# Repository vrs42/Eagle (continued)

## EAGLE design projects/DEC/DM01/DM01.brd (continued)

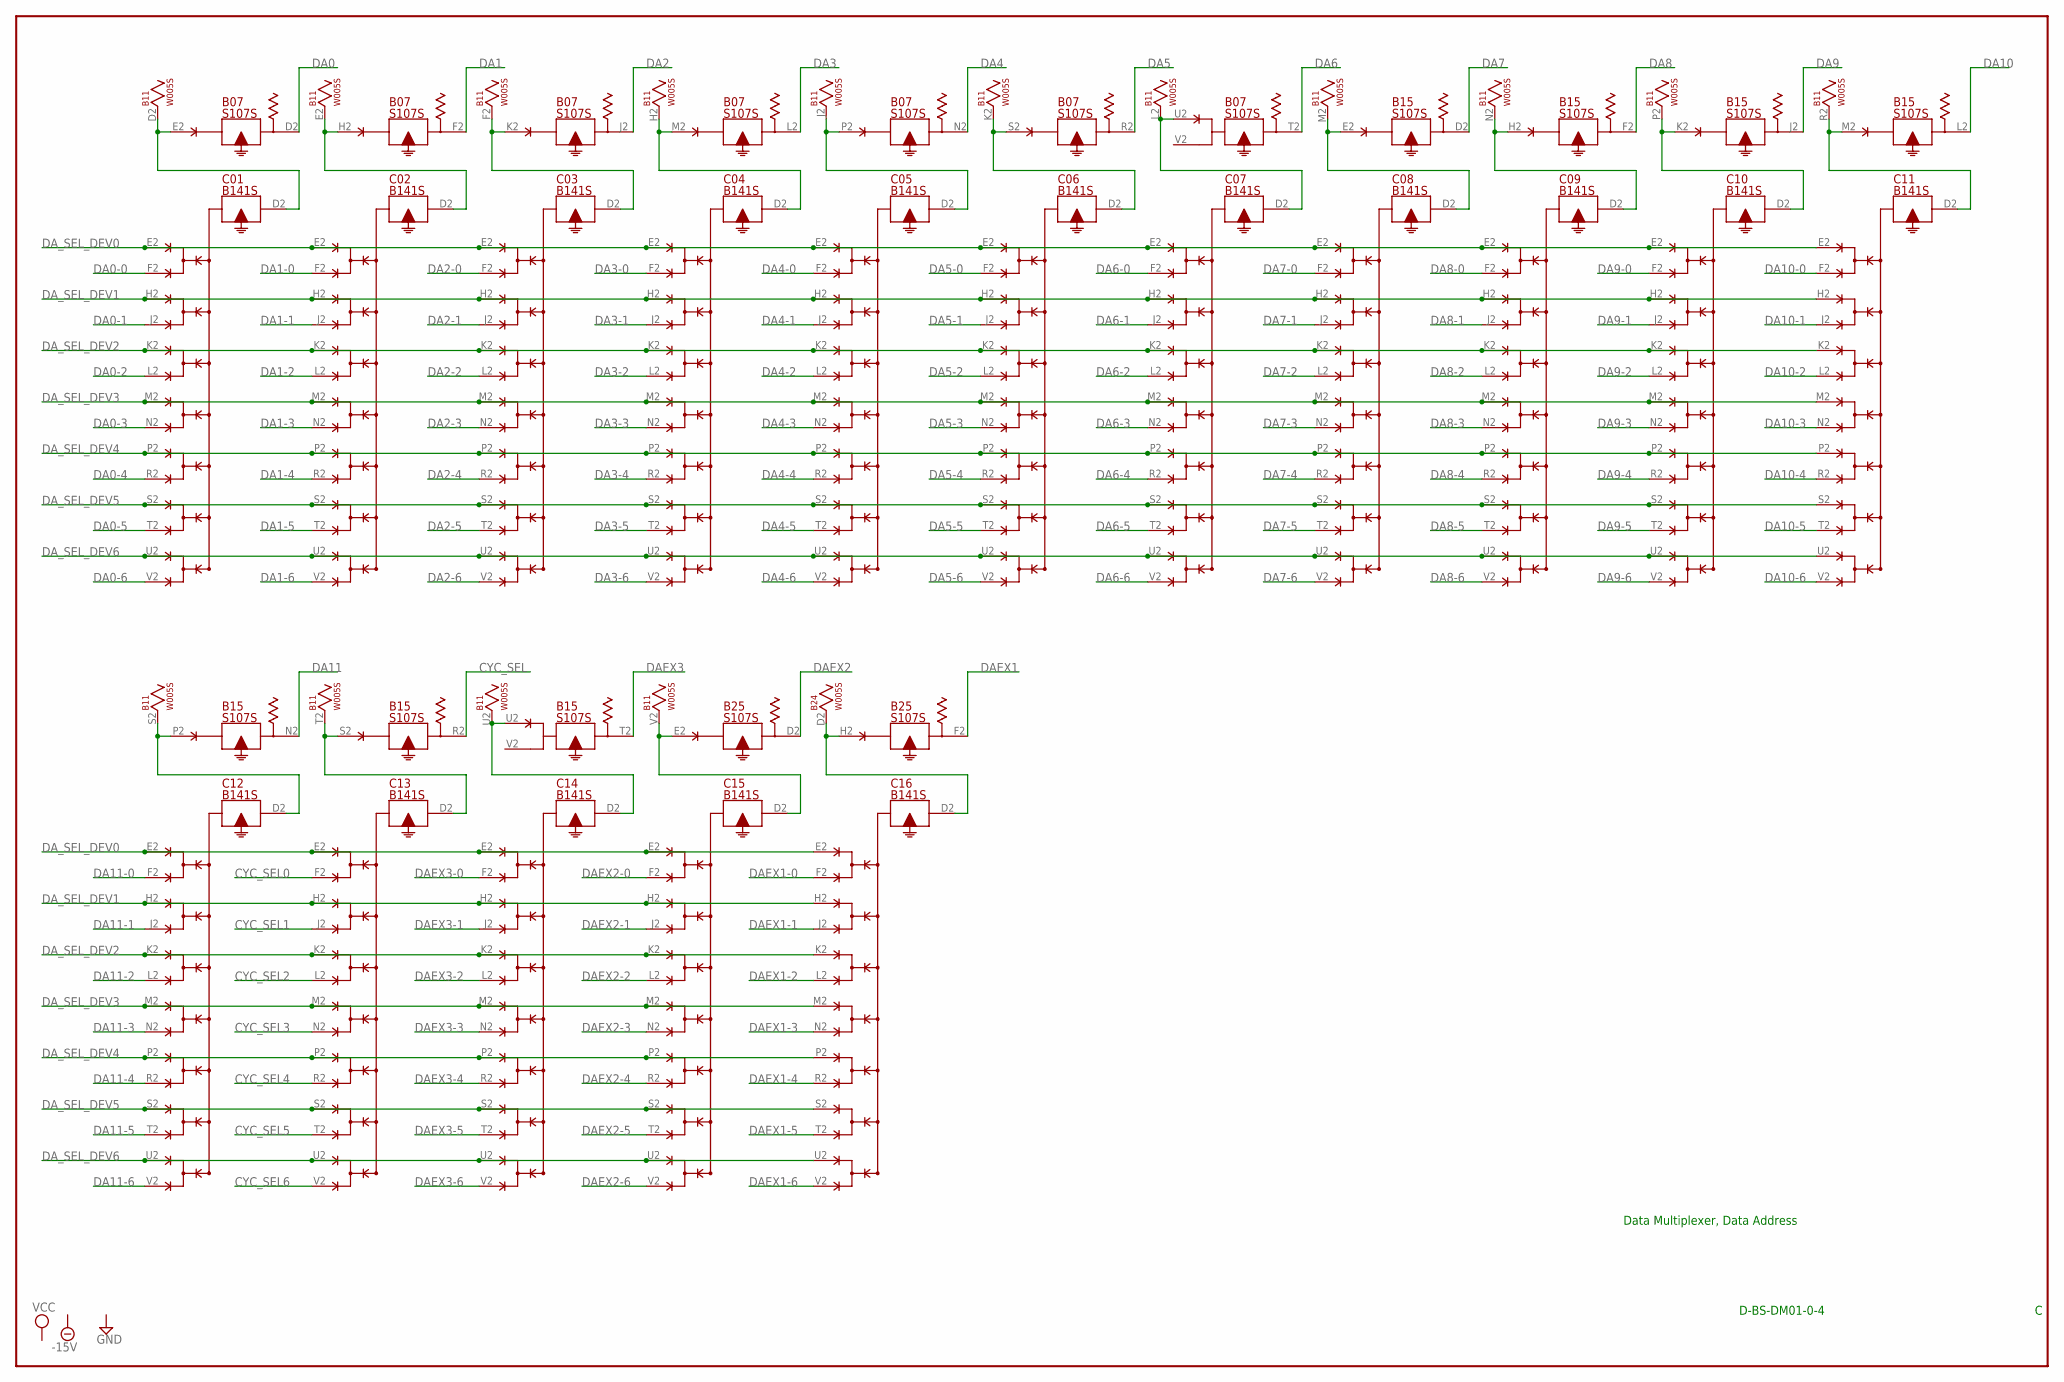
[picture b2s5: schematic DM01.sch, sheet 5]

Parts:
B07, B15, B25: S107S; H807S
B11, B24: W005S; H807S
C01, C02, C03, C04, C05, C06, C07, C08, C09, C10, C11, C12, C13, C14, C15, C16: B141S; H807S

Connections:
-15V: B07.B2 (-15V), B11.B2 (-15V), B15.B2 (-15V), B24.B2 (-15V), B25.B2 (-15V), C01.B2 (-15V), C02.B2 (-15V), C03.B2 (-15V), C04.B2 (-15V), C05.B2 (-15V), C06.B2 (-15V), C07.B2 (-15V), C08.B2 (-15V), C09.B2 (-15V), C10.B2 (-15V), C11.B2 (-15V), C12.B2 (-15V), C13.B2 (-15V), C14.B2 (-15V), C15.B2 (-15V), C16.B2 (-15V); also elsewhere on the board
CYC_SEL: B15.R2; also elsewhere on the board
CYC_SEL0: C13.F2 (F); also elsewhere on the board
CYC_SEL1: C13.J2 (J); also elsewhere on the board
CYC_SEL2: C13.L2 (L); also elsewhere on the board
CYC_SEL3: C13.N2 (N); also elsewhere on the board
CYC_SEL4: C13.R2 (R); also elsewhere on the board
CYC_SEL5: C13.T2 (T); also elsewhere on the board
CYC_SEL6: C13.V2 (V); also elsewhere on the board
DA0: B07.D2; also elsewhere on the board
DA0-0: C01.F2 (F); also elsewhere on the board
DA0-1: C01.J2 (J); also elsewhere on the board
DA0-2: C01.L2 (L); also elsewhere on the board
DA0-3: C01.N2 (N); also elsewhere on the board
DA0-4: C01.R2 (R); also elsewhere on the board
DA0-5: C01.T2 (T); also elsewhere on the board
DA0-6: C01.V2 (V); also elsewhere on the board
DA1: B07.F2; also elsewhere on the board
DA1-0: C02.F2 (F); also elsewhere on the board
DA1-1: C02.J2 (J); also elsewhere on the board
DA1-2: C02.L2 (L); also elsewhere on the board
DA1-3: C02.N2 (N); also elsewhere on the board
DA1-4: C02.R2 (R); also elsewhere on the board
DA1-5: C02.T2 (T); also elsewhere on the board
DA1-6: C02.V2 (V); also elsewhere on the board
DA2: B07.J2; also elsewhere on the board
DA2-0: C03.F2 (F); also elsewhere on the board
DA2-1: C03.J2 (J); also elsewhere on the board
DA2-2: C03.L2 (L); also elsewhere on the board
DA2-3: C03.N2 (N); also elsewhere on the board
DA2-4: C03.R2 (R); also elsewhere on the board
DA2-5: C03.T2 (T); also elsewhere on the board
DA2-6: C03.V2 (V); also elsewhere on the board
DA3: B07.L2; also elsewhere on the board
DA3-0: C04.F2 (F); also elsewhere on the board
DA3-1: C04.J2 (J); also elsewhere on the board
DA3-2: C04.L2 (L); also elsewhere on the board
DA3-3: C04.N2 (N); also elsewhere on the board
DA3-4: C04.R2 (R); also elsewhere on the board
DA3-5: C04.T2 (T); also elsewhere on the board
DA3-6: C04.V2 (V); also elsewhere on the board
DA4: B07.N2; also elsewhere on the board
DA4-0: C05.F2 (F); also elsewhere on the board
DA4-1: C05.J2 (J); also elsewhere on the board
DA4-2: C05.L2 (L); also elsewhere on the board
DA4-3: C05.N2 (N); also elsewhere on the board
DA4-4: C05.R2 (R); also elsewhere on the board
DA4-5: C05.T2 (T); also elsewhere on the board
DA4-6: C05.V2 (V); also elsewhere on the board
DA5: B07.R2; also elsewhere on the board
DA5-0: C06.F2 (F); also elsewhere on the board
DA5-1: C06.J2 (J); also elsewhere on the board
DA5-2: C06.L2 (L); also elsewhere on the board
DA5-3: C06.N2 (N); also elsewhere on the board
DA5-4: C06.R2 (R); also elsewhere on the board
DA5-5: C06.T2 (T); also elsewhere on the board
DA5-6: C06.V2 (V); also elsewhere on the board
DA6: B07.T2; also elsewhere on the board
DA6-0: C07.F2 (F); also elsewhere on the board
DA6-1: C07.J2 (J); also elsewhere on the board
DA6-2: C07.L2 (L); also elsewhere on the board
DA6-3: C07.N2 (N); also elsewhere on the board
DA6-4: C07.R2 (R); also elsewhere on the board
DA6-5: C07.T2 (T); also elsewhere on the board
DA6-6: C07.V2 (V); also elsewhere on the board
DA7: B15.D2; also elsewhere on the board
DA7-0: C08.F2 (F); also elsewhere on the board
DA7-1: C08.J2 (J); also elsewhere on the board
DA7-2: C08.L2 (L); also elsewhere on the board
DA7-3: C08.N2 (N); also elsewhere on the board
DA7-4: C08.R2 (R); also elsewhere on the board
DA7-5: C08.T2 (T); also elsewhere on the board
DA7-6: C08.V2 (V); also elsewhere on the board
DA8: B15.F2; also elsewhere on the board
DA8-0: C09.F2 (F); also elsewhere on the board
DA8-1: C09.J2 (J); also elsewhere on the board
DA8-2: C09.L2 (L); also elsewhere on the board
DA8-3: C09.N2 (N); also elsewhere on the board
DA8-4: C09.R2 (R); also elsewhere on the board
DA8-5: C09.T2 (T); also elsewhere on the board
DA8-6: C09.V2 (V); also elsewhere on the board
DA9: B15.J2; also elsewhere on the board
DA9-0: C10.F2 (F); also elsewhere on the board
DA9-1: C10.J2 (J); also elsewhere on the board
DA9-2: C10.L2 (L); also elsewhere on the board
DA9-3: C10.N2 (N); also elsewhere on the board
DA9-4: C10.R2 (R); also elsewhere on the board
DA9-5: C10.T2 (T); also elsewhere on the board
DA9-6: C10.V2 (V); also elsewhere on the board
DA10: B15.L2; also elsewhere on the board
DA10-0: C11.F2 (F); also elsewhere on the board
DA10-1: C11.J2 (J); also elsewhere on the board
DA10-2: C11.L2 (L); also elsewhere on the board
DA10-3: C11.N2 (N); also elsewhere on the board
DA10-4: C11.R2 (R); also elsewhere on the board
DA10-5: C11.T2 (T); also elsewhere on the board
DA10-6: C11.V2 (V); also elsewhere on the board
DA11: B15.N2; also elsewhere on the board
DA11-0: C12.F2 (F); also elsewhere on the board
DA11-1: C12.J2 (J); also elsewhere on the board
DA11-2: C12.L2 (L); also elsewhere on the board
DA11-3: C12.N2 (N); also elsewhere on the board
DA11-4: C12.R2 (R); also elsewhere on the board
DA11-5: C12.T2 (T); also elsewhere on the board
DA11-6: C12.V2 (V); also elsewhere on the board
DAEX1: B25.F2; also elsewhere on the board
DAEX1-0: C16.F2 (F); also elsewhere on the board
DAEX1-1: C16.J2 (J); also elsewhere on the board
DAEX1-2: C16.L2 (L); also elsewhere on the board
DAEX1-3: C16.N2 (N); also elsewhere on the board
DAEX1-4: C16.R2 (R); also elsewhere on the board
DAEX1-5: C16.T2 (T); also elsewhere on the board
DAEX1-6: C16.V2 (V); also elsewhere on the board
DAEX2: B25.D2; also elsewhere on the board
DAEX2-0: C15.F2 (F); also elsewhere on the board
DAEX2-1: C15.J2 (J); also elsewhere on the board
DAEX2-2: C15.L2 (L); also elsewhere on the board
DAEX2-3: C15.N2 (N); also elsewhere on the board
DAEX2-4: C15.R2 (R); also elsewhere on the board
DAEX2-5: C15.T2 (T); also elsewhere on the board
DAEX2-6: C15.V2 (V); also elsewhere on the board
DAEX3: B15.T2; also elsewhere on the board
DAEX3-0: C14.F2 (F); also elsewhere on the board
DAEX3-1: C14.J2 (J); also elsewhere on the board
DAEX3-2: C14.L2 (L); also elsewhere on the board
DAEX3-3: C14.N2 (N); also elsewhere on the board
DAEX3-4: C14.R2 (R); also elsewhere on the board
DAEX3-5: C14.T2 (T); also elsewhere on the board
DAEX3-6: C14.V2 (V); also elsewhere on the board
DA_SEL_DEV0: C01.E2 (E), C02.E2 (E), C03.E2 (E), C04.E2 (E), C05.E2 (E), C06.E2 (E), C07.E2 (E), C08.E2 (E), C09.E2 (E), C10.E2 (E), C11.E2 (E), C12.E2 (E), C13.E2 (E), C14.E2 (E), C15.E2 (E), C16.E2 (E); also elsewhere on the board
DA_SEL_DEV1: C01.H2 (H), C02.H2 (H), C03.H2 (H), C04.H2 (H), C05.H2 (H), C06.H2 (H), C07.H2 (H), C08.H2 (H), C09.H2 (H), C10.H2 (H), C11.H2 (H), C12.H2 (H), C13.H2 (H), C14.H2 (H), C15.H2 (H), C16.H2 (H); also elsewhere on the board
DA_SEL_DEV2: C01.K2 (K), C02.K2 (K), C03.K2 (K), C04.K2 (K), C05.K2 (K), C06.K2 (K), C07.K2 (K), C08.K2 (K), C09.K2 (K), C10.K2 (K), C11.K2 (K), C12.K2 (K), C13.K2 (K), C14.K2 (K), C15.K2 (K), C16.K2 (K); also elsewhere on the board
DA_SEL_DEV3: C01.M2 (M), C02.M2 (M), C03.M2 (M), C04.M2 (M), C05.M2 (M), C06.M2 (M), C07.M2 (M), C08.M2 (M), C09.M2 (M), C10.M2 (M), C11.M2 (M), C12.M2 (M), C13.M2 (M), C14.M2 (M), C15.M2 (M), C16.M2 (M); also elsewhere on the board
DA_SEL_DEV4: C01.P2, C02.P2, C03.P2, C04.P2, C05.P2, C06.P2, C07.P2, C08.P2, C09.P2, C10.P2, C11.P2, C12.P2, C13.P2, C14.P2, C15.P2, C16.P2; also elsewhere on the board
DA_SEL_DEV5: C01.S2 (S), C02.S2 (S), C03.S2 (S), C04.S2 (S), C05.S2 (S), C06.S2 (S), C07.S2 (S), C08.S2 (S), C09.S2 (S), C10.S2 (S), C11.S2 (S), C12.S2 (S), C13.S2 (S), C14.S2 (S), C15.S2 (S), C16.S2 (S); also elsewhere on the board
DA_SEL_DEV6: C01.U2 (U), C02.U2 (U), C03.U2 (U), C04.U2 (U), C05.U2 (U), C06.U2 (U), C07.U2 (U), C08.U2 (U), C09.U2 (U), C10.U2 (U), C11.U2 (U), C12.U2 (U), C13.U2 (U), C14.U2 (U), C15.U2 (U), C16.U2 (U); also elsewhere on the board
GND: B07.C2 (GND), B11.C2 (GND), B15.C2 (GND), B24.C2 (GND), B25.C2 (GND), C01.C2 (GND), C02.C2 (GND), C03.C2 (GND), C04.C2 (GND), C05.C2 (GND), C06.C2 (GND), C07.C2 (GND), C08.C2 (GND), C09.C2 (GND), C10.C2 (GND), C11.C2 (GND), C12.C2 (GND), C13.C2 (GND), C14.C2 (GND), C15.C2 (GND), C16.C2 (GND); also elsewhere on the board
unnamed: B07.E2, B11.D2, C01.D2 (D)
unnamed: B07.U2, B11.L2, C07.D2 (D)
unnamed: B07.H2, B11.E2, C02.D2 (D)
unnamed: B07.K2, B11.F2, C03.D2 (D)
unnamed: B07.M2, B11.H2, C04.D2 (D)
unnamed: B07.P2, B11.J2, C05.D2 (D)
unnamed: B07.S2, B11.K2, C06.D2 (D)
unnamed: B11.M2, B15.E2, C08.D2 (D)
unnamed: B11.N2, B15.H2, C09.D2 (D)
unnamed: B11.P2, B15.K2, C10.D2 (D)
unnamed: B11.R2, B15.M2, C11.D2 (D)
unnamed: B11.S2, B15.P2, C12.D2 (D)
unnamed: B11.T2, B15.S2, C13.D2 (D)
unnamed: B11.U2, B15.U2, C14.D2 (D)
unnamed: B11.V2, B25.E2, C15.D2 (D)
unnamed: B24.D2, B25.H2, C16.D2 (D)
VCC: B07.A2 (VCC), B11.A2 (VCC), B15.A2 (VCC), B24.A2 (VCC), B25.A2 (VCC), C01.A2 (VCC), C02.A2 (VCC), C03.A2 (VCC), C04.A2 (VCC), C05.A2 (VCC), C06.A2 (VCC), C07.A2 (VCC), C08.A2 (VCC), C09.A2 (VCC), C10.A2 (VCC), C11.A2 (VCC), C12.A2 (VCC), C13.A2 (VCC), C14.A2 (VCC), C15.A2 (VCC), C16.A2 (VCC); also elsewhere on the board

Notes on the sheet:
D-BS-DM01-0-4
Data Multiplexer, Data Address

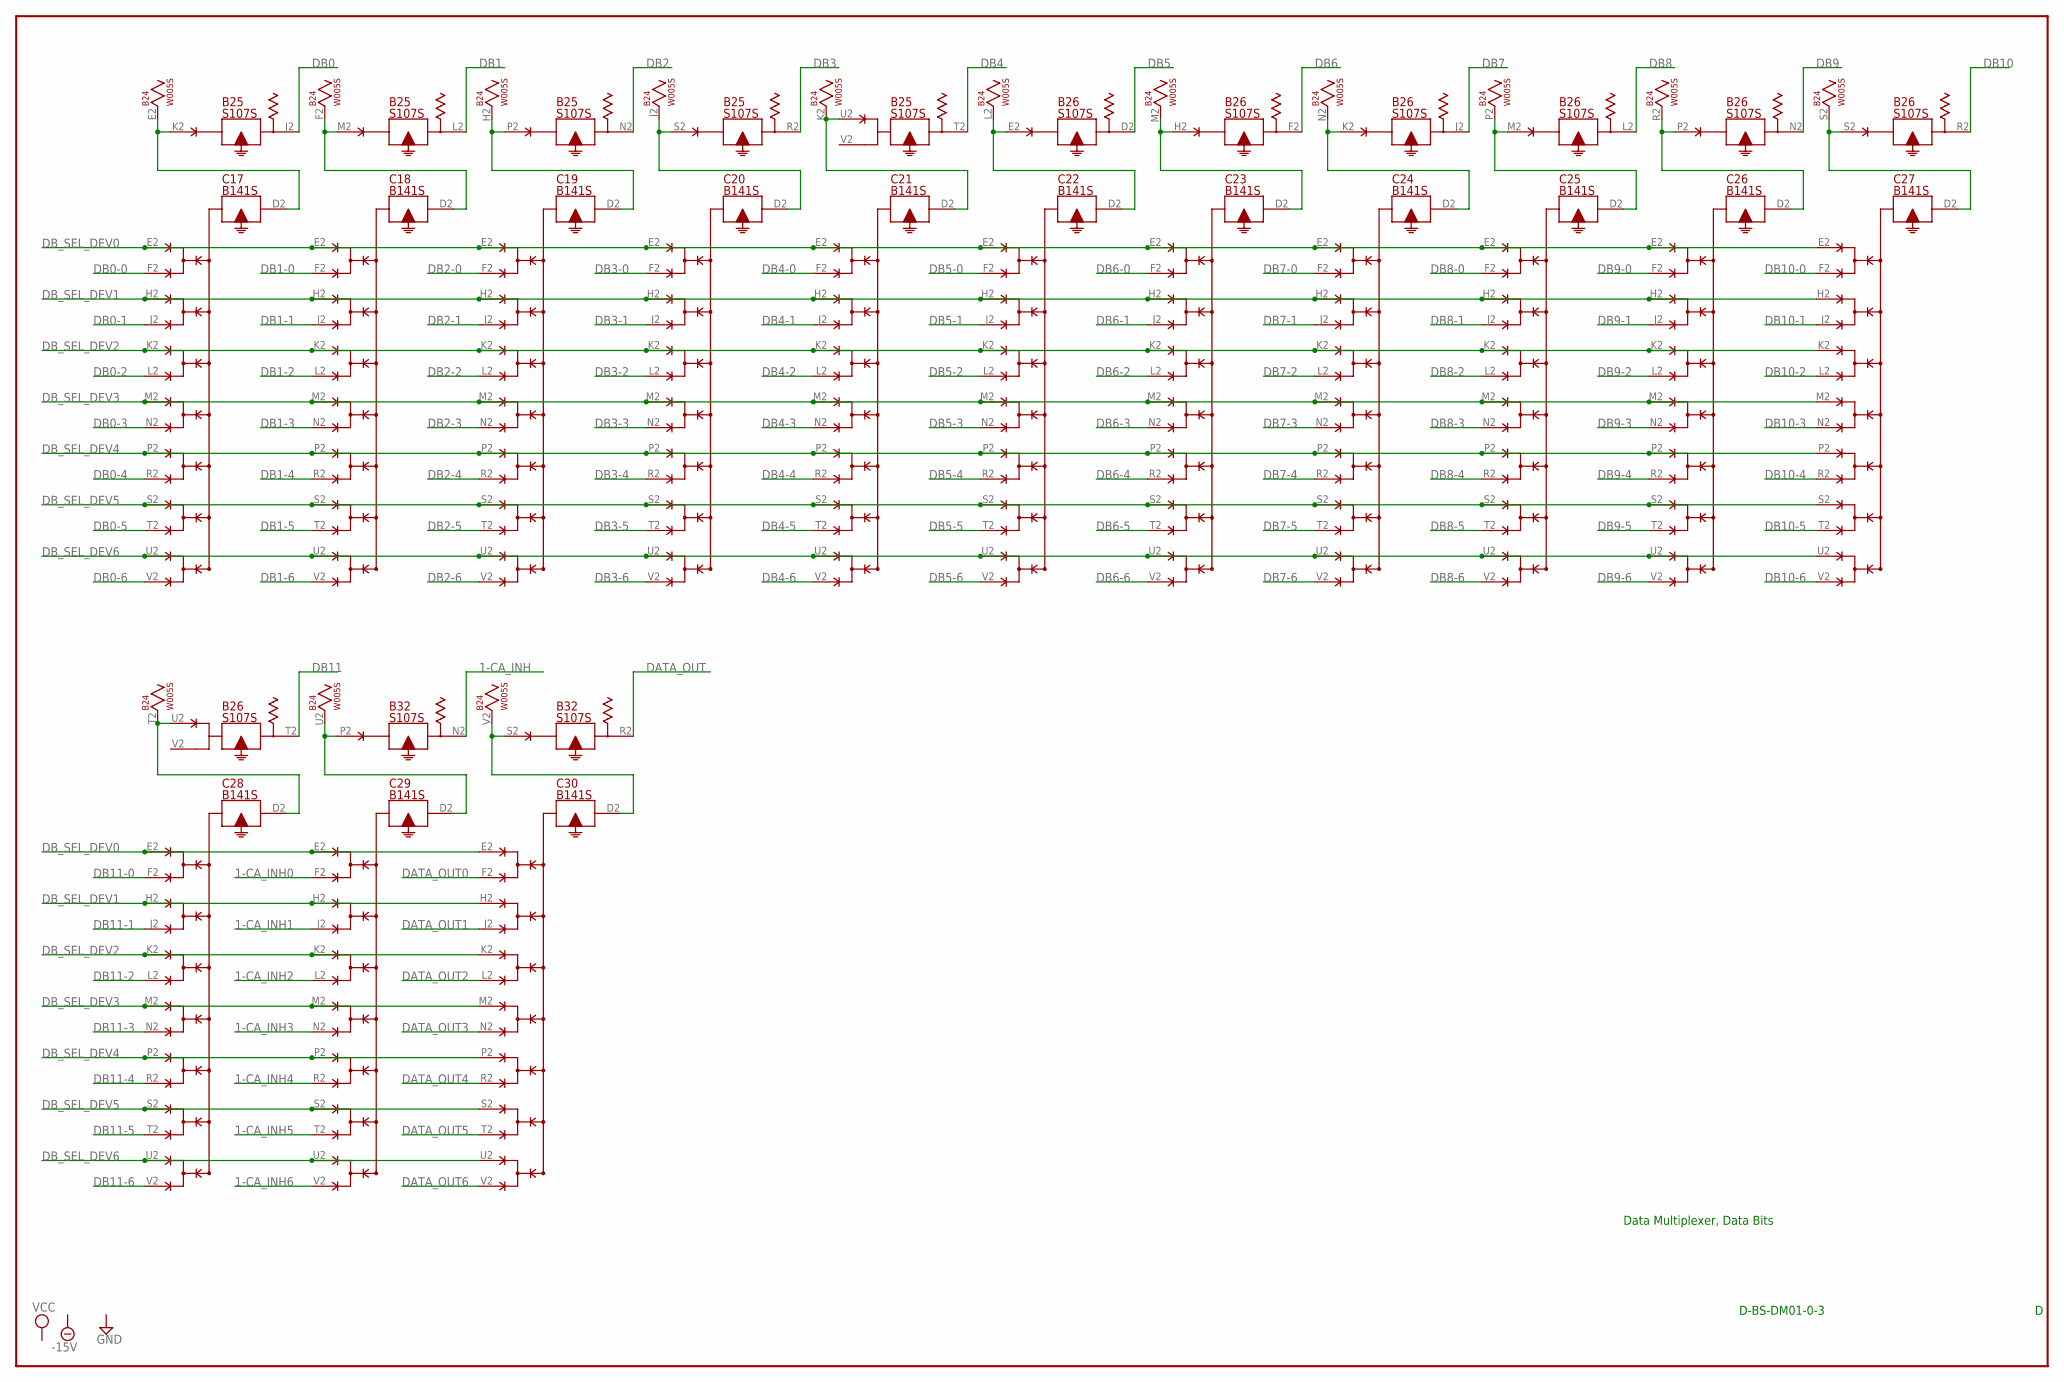
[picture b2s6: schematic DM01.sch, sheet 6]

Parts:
B24: W005S; H807S
B25, B26, B32: S107S; H807S
C17, C18, C19, C20, C21, C22, C23, C24, C25, C26, C27, C28, C29, C30: B141S; H807S

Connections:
1-CA_INH: B32.N2; also elsewhere on the board
1-CA_INH0: C29.F2 (F); also elsewhere on the board
1-CA_INH1: C29.J2 (J); also elsewhere on the board
1-CA_INH2: C29.L2 (L); also elsewhere on the board
1-CA_INH3: C29.N2 (N); also elsewhere on the board
1-CA_INH4: C29.R2 (R); also elsewhere on the board
1-CA_INH5: C29.T2 (T); also elsewhere on the board
1-CA_INH6: C29.V2 (V); also elsewhere on the board
-15V: B24.B2 (-15V), B25.B2 (-15V), B26.B2 (-15V), B32.B2 (-15V), C17.B2 (-15V), C18.B2 (-15V), C19.B2 (-15V), C20.B2 (-15V), C21.B2 (-15V), C22.B2 (-15V), C23.B2 (-15V), C24.B2 (-15V), C25.B2 (-15V), C26.B2 (-15V), C27.B2 (-15V), C28.B2 (-15V), C29.B2 (-15V), C30.B2 (-15V); also elsewhere on the board
DATA_OUT: B32.R2; also elsewhere on the board
DATA_OUT0: C30.F2 (F); also elsewhere on the board
DATA_OUT1: C30.J2 (J); also elsewhere on the board
DATA_OUT2: C30.L2 (L); also elsewhere on the board
DATA_OUT3: C30.N2 (N); also elsewhere on the board
DATA_OUT4: C30.R2 (R); also elsewhere on the board
DATA_OUT5: C30.T2 (T); also elsewhere on the board
DATA_OUT6: C30.V2 (V); also elsewhere on the board
DB0: B25.J2; also elsewhere on the board
DB0-0: C17.F2 (F); also elsewhere on the board
DB0-1: C17.J2 (J); also elsewhere on the board
DB0-2: C17.L2 (L); also elsewhere on the board
DB0-3: C17.N2 (N); also elsewhere on the board
DB0-4: C17.R2 (R); also elsewhere on the board
DB0-5: C17.T2 (T); also elsewhere on the board
DB0-6: C17.V2 (V); also elsewhere on the board
DB1: B25.L2; also elsewhere on the board
DB1-0: C18.F2 (F); also elsewhere on the board
DB1-1: C18.J2 (J); also elsewhere on the board
DB1-2: C18.L2 (L); also elsewhere on the board
DB1-3: C18.N2 (N); also elsewhere on the board
DB1-4: C18.R2 (R); also elsewhere on the board
DB1-5: C18.T2 (T); also elsewhere on the board
DB1-6: C18.V2 (V); also elsewhere on the board
DB2: B25.N2; also elsewhere on the board
DB2-0: C19.F2 (F); also elsewhere on the board
DB2-1: C19.J2 (J); also elsewhere on the board
DB2-2: C19.L2 (L); also elsewhere on the board
DB2-3: C19.N2 (N); also elsewhere on the board
DB2-4: C19.R2 (R); also elsewhere on the board
DB2-5: C19.T2 (T); also elsewhere on the board
DB2-6: C19.V2 (V); also elsewhere on the board
DB3: B25.R2; also elsewhere on the board
DB3-0: C20.F2 (F); also elsewhere on the board
DB3-1: C20.J2 (J); also elsewhere on the board
DB3-2: C20.L2 (L); also elsewhere on the board
DB3-3: C20.N2 (N); also elsewhere on the board
DB3-4: C20.R2 (R); also elsewhere on the board
DB3-5: C20.T2 (T); also elsewhere on the board
DB3-6: C20.V2 (V); also elsewhere on the board
DB4: B25.T2; also elsewhere on the board
DB4-0: C21.F2 (F); also elsewhere on the board
DB4-1: C21.J2 (J); also elsewhere on the board
DB4-2: C21.L2 (L); also elsewhere on the board
DB4-3: C21.N2 (N); also elsewhere on the board
DB4-4: C21.R2 (R); also elsewhere on the board
DB4-5: C21.T2 (T); also elsewhere on the board
DB4-6: C21.V2 (V); also elsewhere on the board
DB5: B26.D2; also elsewhere on the board
DB5-0: C22.F2 (F); also elsewhere on the board
DB5-1: C22.J2 (J); also elsewhere on the board
DB5-2: C22.L2 (L); also elsewhere on the board
DB5-3: C22.N2 (N); also elsewhere on the board
DB5-4: C22.R2 (R); also elsewhere on the board
DB5-5: C22.T2 (T); also elsewhere on the board
DB5-6: C22.V2 (V); also elsewhere on the board
DB6: B26.F2; also elsewhere on the board
DB6-0: C23.F2 (F); also elsewhere on the board
DB6-1: C23.J2 (J); also elsewhere on the board
DB6-2: C23.L2 (L); also elsewhere on the board
DB6-3: C23.N2 (N); also elsewhere on the board
DB6-4: C23.R2 (R); also elsewhere on the board
DB6-5: C23.T2 (T); also elsewhere on the board
DB6-6: C23.V2 (V); also elsewhere on the board
DB7: B26.J2; also elsewhere on the board
DB7-0: C24.F2 (F); also elsewhere on the board
DB7-1: C24.J2 (J); also elsewhere on the board
DB7-2: C24.L2 (L); also elsewhere on the board
DB7-3: C24.N2 (N); also elsewhere on the board
DB7-4: C24.R2 (R); also elsewhere on the board
DB7-5: C24.T2 (T); also elsewhere on the board
DB7-6: C24.V2 (V); also elsewhere on the board
DB8: B26.L2; also elsewhere on the board
DB8-0: C25.F2 (F); also elsewhere on the board
DB8-1: C25.J2 (J); also elsewhere on the board
DB8-2: C25.L2 (L); also elsewhere on the board
DB8-3: C25.N2 (N); also elsewhere on the board
DB8-4: C25.R2 (R); also elsewhere on the board
DB8-5: C25.T2 (T); also elsewhere on the board
DB8-6: C25.V2 (V); also elsewhere on the board
DB9: B26.N2; also elsewhere on the board
DB9-0: C26.F2 (F); also elsewhere on the board
DB9-1: C26.J2 (J); also elsewhere on the board
DB9-2: C26.L2 (L); also elsewhere on the board
DB9-3: C26.N2 (N); also elsewhere on the board
DB9-4: C26.R2 (R); also elsewhere on the board
DB9-5: C26.T2 (T); also elsewhere on the board
DB9-6: C26.V2 (V); also elsewhere on the board
DB10: B26.R2; also elsewhere on the board
DB10-0: C27.F2 (F); also elsewhere on the board
DB10-1: C27.J2 (J); also elsewhere on the board
DB10-2: C27.L2 (L); also elsewhere on the board
DB10-3: C27.N2 (N); also elsewhere on the board
DB10-4: C27.R2 (R); also elsewhere on the board
DB10-5: C27.T2 (T); also elsewhere on the board
DB10-6: C27.V2 (V); also elsewhere on the board
DB11: B26.T2; also elsewhere on the board
DB11-0: C28.F2 (F); also elsewhere on the board
DB11-1: C28.J2 (J); also elsewhere on the board
DB11-2: C28.L2 (L); also elsewhere on the board
DB11-3: C28.N2 (N); also elsewhere on the board
DB11-4: C28.R2 (R); also elsewhere on the board
DB11-5: C28.T2 (T); also elsewhere on the board
DB11-6: C28.V2 (V); also elsewhere on the board
DB_SEL_DEV0: C17.E2 (E), C18.E2 (E), C19.E2 (E), C20.E2 (E), C21.E2 (E), C22.E2 (E), C23.E2 (E), C24.E2 (E), C25.E2 (E), C26.E2 (E), C27.E2 (E), C28.E2 (E), C29.E2 (E), C30.E2 (E); also elsewhere on the board
DB_SEL_DEV1: C17.H2 (H), C18.H2 (H), C19.H2 (H), C20.H2 (H), C21.H2 (H), C22.H2 (H), C23.H2 (H), C24.H2 (H), C25.H2 (H), C26.H2 (H), C27.H2 (H), C28.H2 (H), C29.H2 (H), C30.H2 (H); also elsewhere on the board
DB_SEL_DEV2: C17.K2 (K), C18.K2 (K), C19.K2 (K), C20.K2 (K), C21.K2 (K), C22.K2 (K), C23.K2 (K), C24.K2 (K), C25.K2 (K), C26.K2 (K), C27.K2 (K), C28.K2 (K), C29.K2 (K), C30.K2 (K); also elsewhere on the board
DB_SEL_DEV3: C17.M2 (M), C18.M2 (M), C19.M2 (M), C20.M2 (M), C21.M2 (M), C22.M2 (M), C23.M2 (M), C24.M2 (M), C25.M2 (M), C26.M2 (M), C27.M2 (M), C28.M2 (M), C29.M2 (M), C30.M2 (M); also elsewhere on the board
DB_SEL_DEV4: C17.P2, C18.P2, C19.P2, C20.P2, C21.P2, C22.P2, C23.P2, C24.P2, C25.P2, C26.P2, C27.P2, C28.P2, C29.P2, C30.P2; also elsewhere on the board
DB_SEL_DEV5: C17.S2 (S), C18.S2 (S), C19.S2 (S), C20.S2 (S), C21.S2 (S), C22.S2 (S), C23.S2 (S), C24.S2 (S), C25.S2 (S), C26.S2 (S), C27.S2 (S), C28.S2 (S), C29.S2 (S), C30.S2 (S); also elsewhere on the board
DB_SEL_DEV6: C17.U2 (U), C18.U2 (U), C19.U2 (U), C20.U2 (U), C21.U2 (U), C22.U2 (U), C23.U2 (U), C24.U2 (U), C25.U2 (U), C26.U2 (U), C27.U2 (U), C28.U2 (U), C29.U2 (U), C30.U2 (U); also elsewhere on the board
GND: B24.C2 (GND), B25.C2 (GND), B26.C2 (GND), B32.C2 (GND), C17.C2 (GND), C18.C2 (GND), C19.C2 (GND), C20.C2 (GND), C21.C2 (GND), C22.C2 (GND), C23.C2 (GND), C24.C2 (GND), C25.C2 (GND), C26.C2 (GND), C27.C2 (GND), C28.C2 (GND), C29.C2 (GND), C30.C2 (GND); also elsewhere on the board
unnamed: B24.E2, B25.K2, C17.D2 (D)
unnamed: B24.F2, B25.M2, C18.D2 (D)
unnamed: B24.H2, B25.P2, C19.D2 (D)
unnamed: B24.J2, B25.S2, C20.D2 (D)
unnamed: B24.K2, B25.U2, C21.D2 (D)
unnamed: B24.L2, B26.E2, C22.D2 (D)
unnamed: B24.M2, B26.H2, C23.D2 (D)
unnamed: B24.N2, B26.K2, C24.D2 (D)
unnamed: B24.P2, B26.M2, C25.D2 (D)
unnamed: B24.R2, B26.P2, C26.D2 (D)
unnamed: B24.S2, B26.S2, C27.D2 (D)
unnamed: B24.T2, B26.U2, C28.D2 (D)
unnamed: B24.U2, B32.P2, C29.D2 (D)
unnamed: B24.V2, B32.S2, C30.D2 (D)
VCC: B24.A2 (VCC), B25.A2 (VCC), B26.A2 (VCC), B32.A2 (VCC), C17.A2 (VCC), C18.A2 (VCC), C19.A2 (VCC), C20.A2 (VCC), C21.A2 (VCC), C22.A2 (VCC), C23.A2 (VCC), C24.A2 (VCC), C25.A2 (VCC), C26.A2 (VCC), C27.A2 (VCC), C28.A2 (VCC), C29.A2 (VCC), C30.A2 (VCC); also elsewhere on the board

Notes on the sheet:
D-BS-DM01-0-3
Data Multiplexer, Data Bits

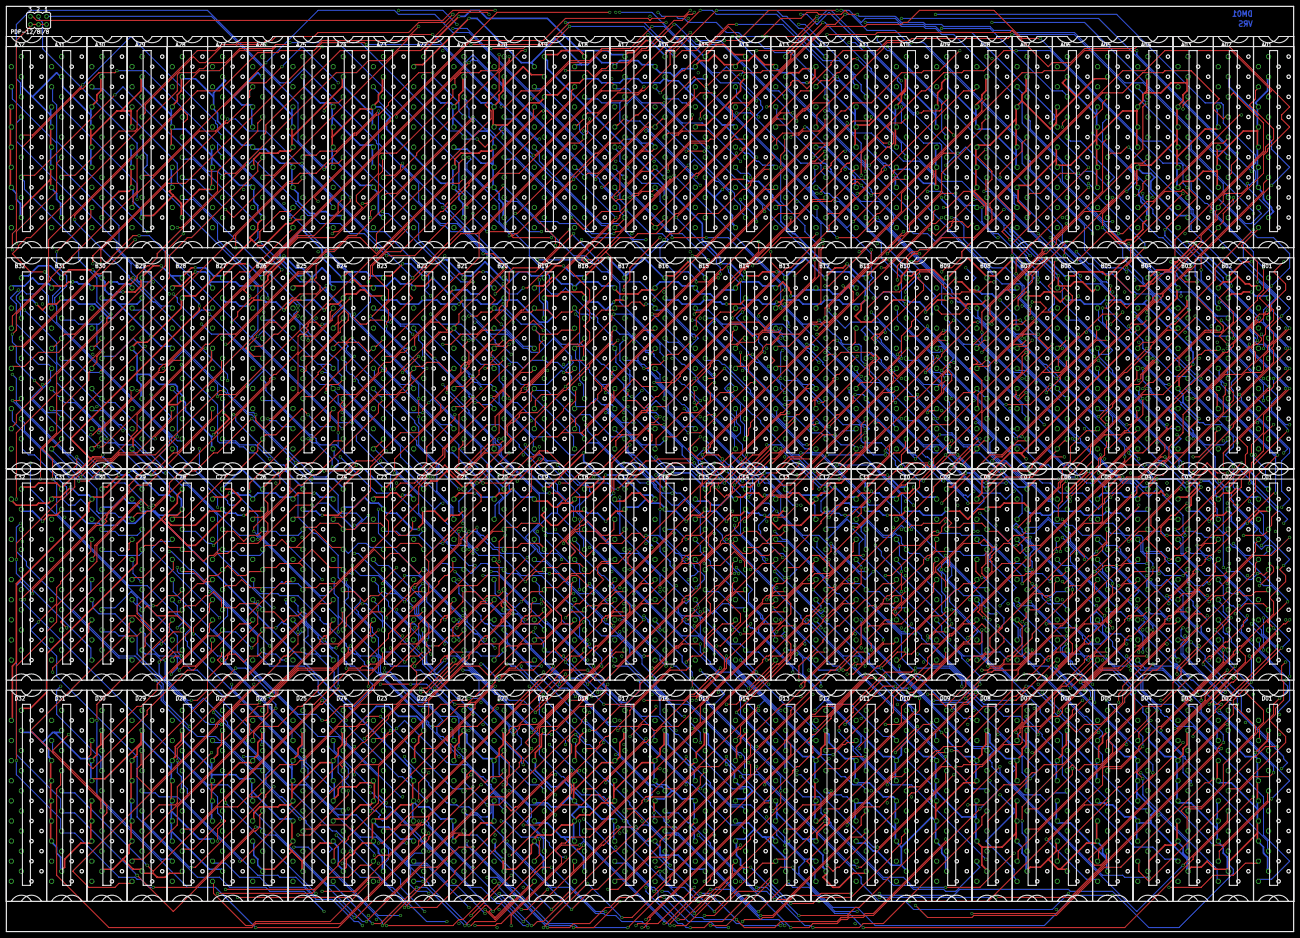
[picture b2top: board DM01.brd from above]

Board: 4 copper layers, 406.4 x 292.1 mm, 145 parts (0 on the bottom side), 444 nets.

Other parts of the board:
U$1, U$2, U$3, U$4, U$5, U$6, U$7, U$8, U$9, U$10, U$11, U$12, U$13, U$14, U$15, U$16: CBLOCK

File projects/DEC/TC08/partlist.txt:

Partlist

Exported from tc08.sch at  8/08/2006 10:36:56a

EAGLE Version 4.11 Copyright (c) 1988-2003 CadSoft

Part     Value          Device     Package  Library  Sheet

A02      M903           M903       H807     dec-m    12
A03      M903           M903       H807     dec-m    12
A04      M903           M903       H807     dec-m    12
A05      M903           M903       H807     dec-m    12
A06      M903           M903       H807     dec-m    12
A07      M161           M161       H807     dec-m    2
A08      M206           M206X      H807     dec-m    4
A09      M117           M117       H807     dec-m    2
A10      M113           M113       H807     dec-m    2
A11      M111           M111       H807     dec-m    1
A12      M113           M113       H807     dec-m    1
A14      M302           M302       H807     dec-m    3
A15      M627           M627       H807     dec-m    3
A16      M602           M602       H807     dec-m    3
A18      G888           G888       H807     dec-m    10
A20      G888           G888       H807     dec-m    10
A21      G888           G888       H807     dec-m    10
A22      M502           M502       H807     dec-m    2
A23      M633           M633       H807     dec-m    2
A24      W023           W023       H807     dec-m    12
A25      M916           M916       H807     dec-m    12
A26      M916           M916       H807     dec-m    12
AB01     G821           G821       H807-2   dec-m    10
AB19     W032           W032       H807-2   dec-m    10
B02      M623           M623       H807     dec-m    11
B03      M623           M623       H807     dec-m    11
B04      M623           M623       H807     dec-m    11
B05      M623           M623       H807     dec-m    11
B06      M111           M111       H807     dec-m    1
B07      M207           M207       H807     dec-m    2
B08      M113           M113       H807     dec-m    1
B09      M206           M206X      H807     dec-m    8
B10      M627           M627       H807     dec-m    1
B11      M115           M115       H807     dec-m    2
B12      M117           M117       H807     dec-m    4
B13      M206           M206X      H807     dec-m    4
B14      M206           M206X      H807     dec-m    2
B15      M113           M113       H807     dec-m    3
B16      M602           M602       H807     dec-m    3
B18      G888           G888       H807     dec-m    10
B20      G888           G888       H807     dec-m    10
B21      G879           G879       H807     dec-m    6
B22      M633           M633       H807     dec-m    2
B23      W005           W005       H807     dec-m    2
C01      M101           M101       H807     dec-m    1
C02      M101           M101-ARRAY H807     dec-m    11
C03      M101           M101-ARRAY H807     dec-m    11
C04      M103           M103       H807     dec-m    1
C05      M103           M103       H807     dec-m    1
C06      M111           M111       H807     dec-m    1
C07      M207           M207       H807     dec-m    2
C08      M121           M121       H807     dec-m    1
C09      M206           M206X      H807     dec-m    8
C10      M121           M121       H807     dec-m    6
C11      M113           M113       H807     dec-m    4
C12      M115           M115       H807     dec-m    3
C13      M111           M111       H807     dec-m    3
C14      M206           M206X      H807     dec-m    3
C15      M113           M113       H807     dec-m    3
C16      M627           M627       H807     dec-m    1
C17      M111           M111       H807     dec-m    1
CD18     M228           M228       H807-2   dec-m    7
D02      M903           M903       H807     dec-m    12
D03      M903           M903       H807     dec-m    12
D04      M903           M903       H807     dec-m    12
D05      M903           M903       H807     dec-m    12
D06      M903           M903       H807     dec-m    12
D07      M161           M161       H807     dec-m    2
D08      M207           M207       H807     dec-m    9
D09      M121           M121       H807     dec-m    2
D10      M119           M119       H807     dec-m    3
D11      M206           M206X      H807     dec-m    1
D12      M627           M627       H807     dec-m    1
D13      M602           M602       H807     dec-m    1
D14      M307           M307       H807     dec-m    3
D15      M401           M401       H807     dec-m    3
D16      M302           M302       H807     dec-m    6
D17      M602           M602       H807     dec-m    1
